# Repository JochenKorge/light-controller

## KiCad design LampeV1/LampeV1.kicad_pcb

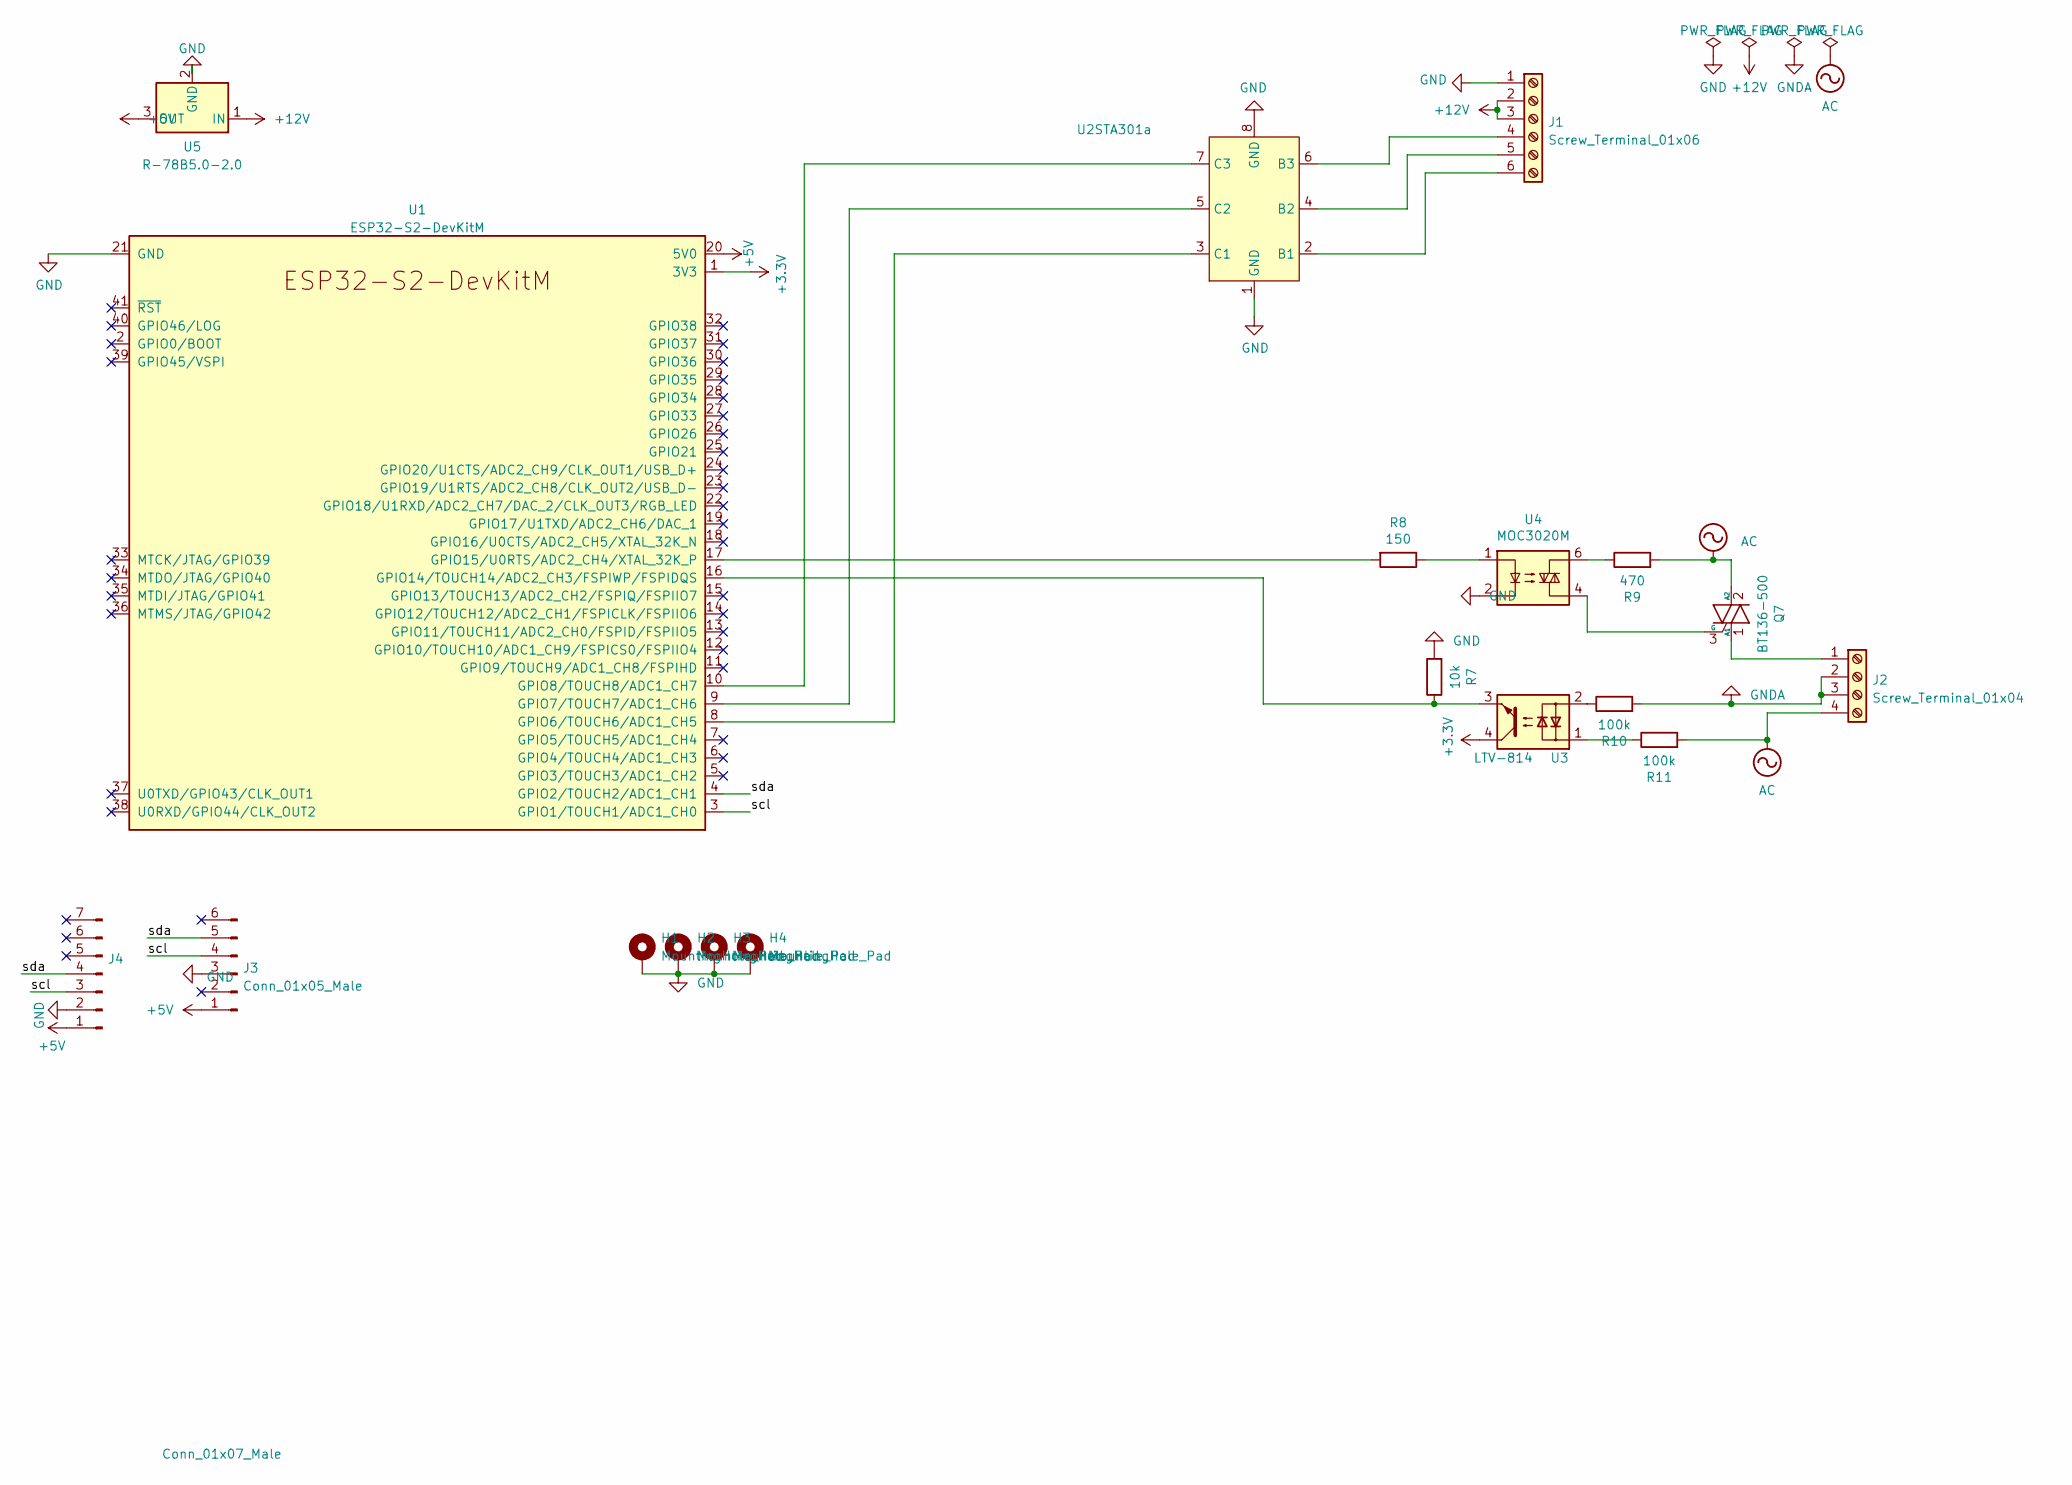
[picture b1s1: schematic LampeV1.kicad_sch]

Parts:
H1, H2, H3, H4: MountingHole_Pad; MountingHole_2.7mm_M2.5_ISO14580_Pad_TopBottom
J1: Screw_Terminal_01x06; TerminalBlock_MetzConnect_Type094_RT03506HBLU_1x06_P5.00mm_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
J2: Screw_Terminal_01x04; TerminalBlock_MetzConnect_Type094_RT03504HBLU_1x04_P5.00mm_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
J3: Conn_01x05_Male; LTR390
J4: Conn_01x07_Male; scd30
Q7: BT136-500; TO-220-3_Vertical
R7: 10k; R_Axial_DIN0207_L6.3mm_D2.5mm_P7.62mm_Horizontal
R8: 150; R_Axial_DIN0207_L6.3mm_D2.5mm_P7.62mm_Horizontal
R9: 470; R_Axial_DIN0207_L6.3mm_D2.5mm_P7.62mm_Horizontal
R10, R11: 100k; R_Axial_DIN0207_L6.3mm_D2.5mm_P7.62mm_Horizontal
U1: ESP32-S2-DevKitM
U2: STA301a; SIP-8_19x3mm_P2.54mm
U3: LTV-814; DIP-4_W7.62mm
U4: MOC3020M; DIP-6_W7.62mm
U5: R-78B5.0-2.0; Converter_DCDC_RECOM_R-78B-2.0_THT

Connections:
+3V3: U1.1 (3V3), U3.4
+5V: J3.1, J4.1, U1.20 (5V0), U5.3 (OUT)
+12V: J1.2, J1.3, U5.1 (IN)
/scl: J3.4, J4.3, U1.3 (GPIO1/TOUCH1/ADC1_CH0)
/sda: J3.5, J4.4, U1.4 (GPIO2/TOUCH2/ADC1_CH1)
AC: J2.4, Q7.2 (A2), R9.2, R11.2
GND: H1.1, H2.1, H3.1, H4.1, J1.1, J3.3, J4.2, R7.2, U1.21 (GND), U1.42 (GND), U2.1 (GND), U2.8 (GND), U4.2, U5.2 (GND)
GNDA: J2.2, J2.3, R10.2
unnamed: J1.4, U2.6 (B3)
unnamed: J1.5, U2.4 (B2)
unnamed: J1.6, U2.2 (B1)
unnamed: J2.1, Q7.1 (A1)
unnamed: Q7.3 (G), U4.4
unnamed: R7.1, U1.16 (GPIO14/TOUCH14/ADC2_CH3/FSPIWP/FSPIDQS), U3.3
unnamed: R8.1, U4.1
unnamed: R8.2, U1.17 (GPIO15/U0RTS/ADC2_CH4/XTAL_32K_P)
unnamed: R9.1, U4.6
unnamed: R10.1, U3.2
unnamed: R11.1, U3.1
unnamed: U1.8 (GPIO6/TOUCH6/ADC1_CH5), U2.3 (C1)
unnamed: U1.9 (GPIO7/TOUCH7/ADC1_CH6), U2.5 (C2)
unnamed: U1.10 (GPIO8/TOUCH8/ADC1_CH7), U2.7 (C3)

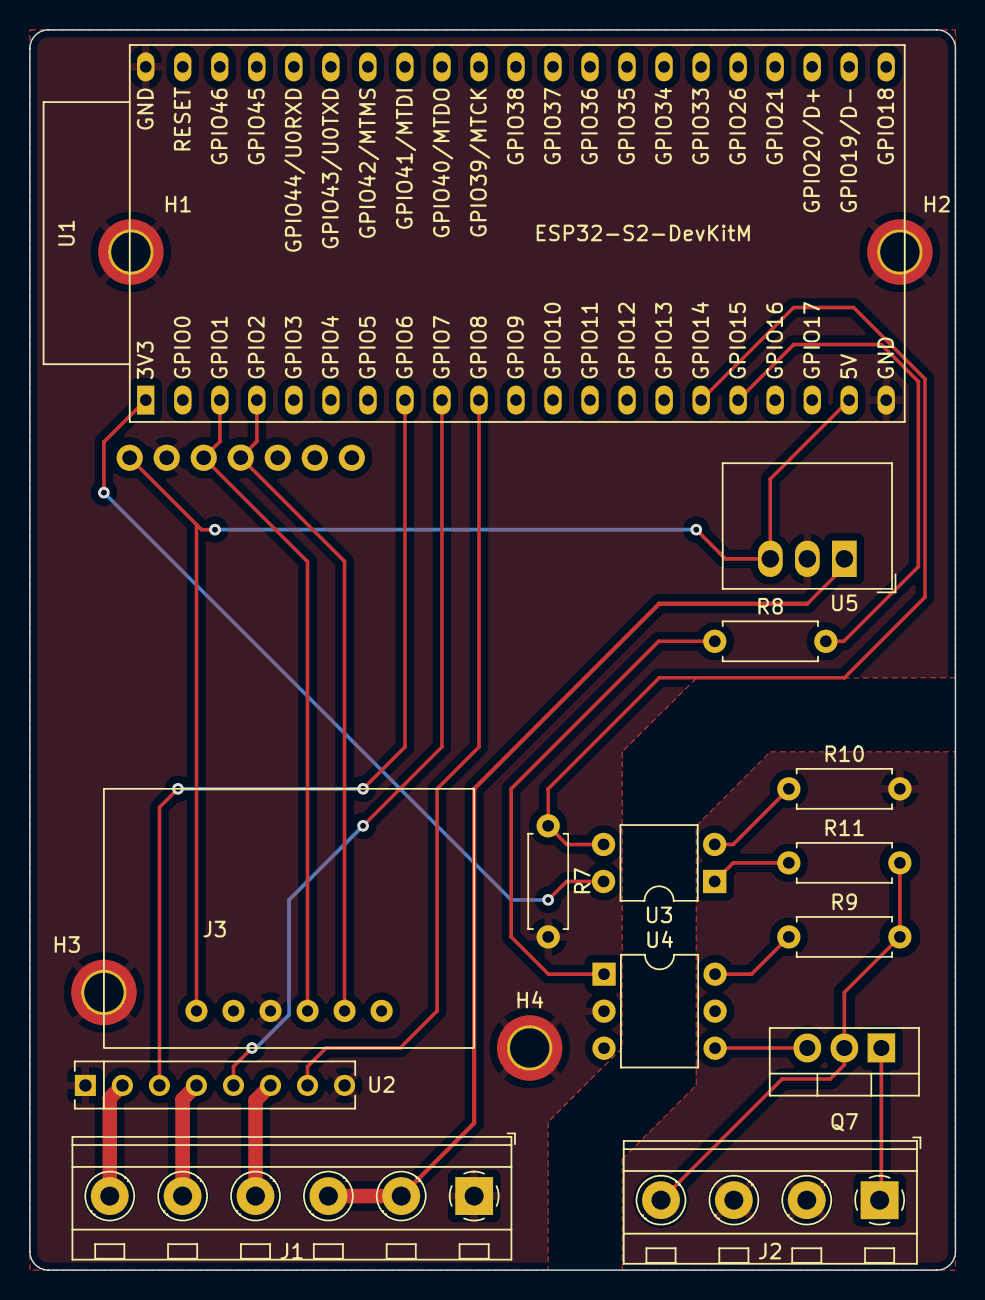
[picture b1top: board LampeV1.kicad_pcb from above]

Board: 2 copper layers, 63.5 x 85.1 mm, 19 parts (0 on the bottom side), 22 nets.

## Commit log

2023-04-07 gerber done
2023-04-08 Added Drillmap
2023-05-22 added case
